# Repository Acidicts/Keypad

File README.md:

# A Numpad or Keypad
## Do as you please with it

It has:
- 16 standard 1:1 aspect ratio keys
- A 1:2 aspect ratio key
- Rotary Encoder
- Seeed Studio Xiao RP2040

The order of assembly/soldering is:
- The Diodes
- The Seeed Studio Xiao RP2040
- The Rotary Encoder
- Keys
- Keycaps Encoder Knob

This is yet to have firmware made for it as it is easier to debug with the actual hardware on hand.
Will be using either **KMK** or **QMK** most likely (kmk due to being easier to learn) and will be referencing [this](https://github.com/Acidicts/Hackpad)

The Rotary Encoder can be used as an audio knob all the way to being a selector for presets for different key setups.

Here is a render of the finished product:

Case:

<div>

</div>

https://github.com/user-attachments/assets/b589e256-21bc-4e0a-8186-24f3bf2696fe

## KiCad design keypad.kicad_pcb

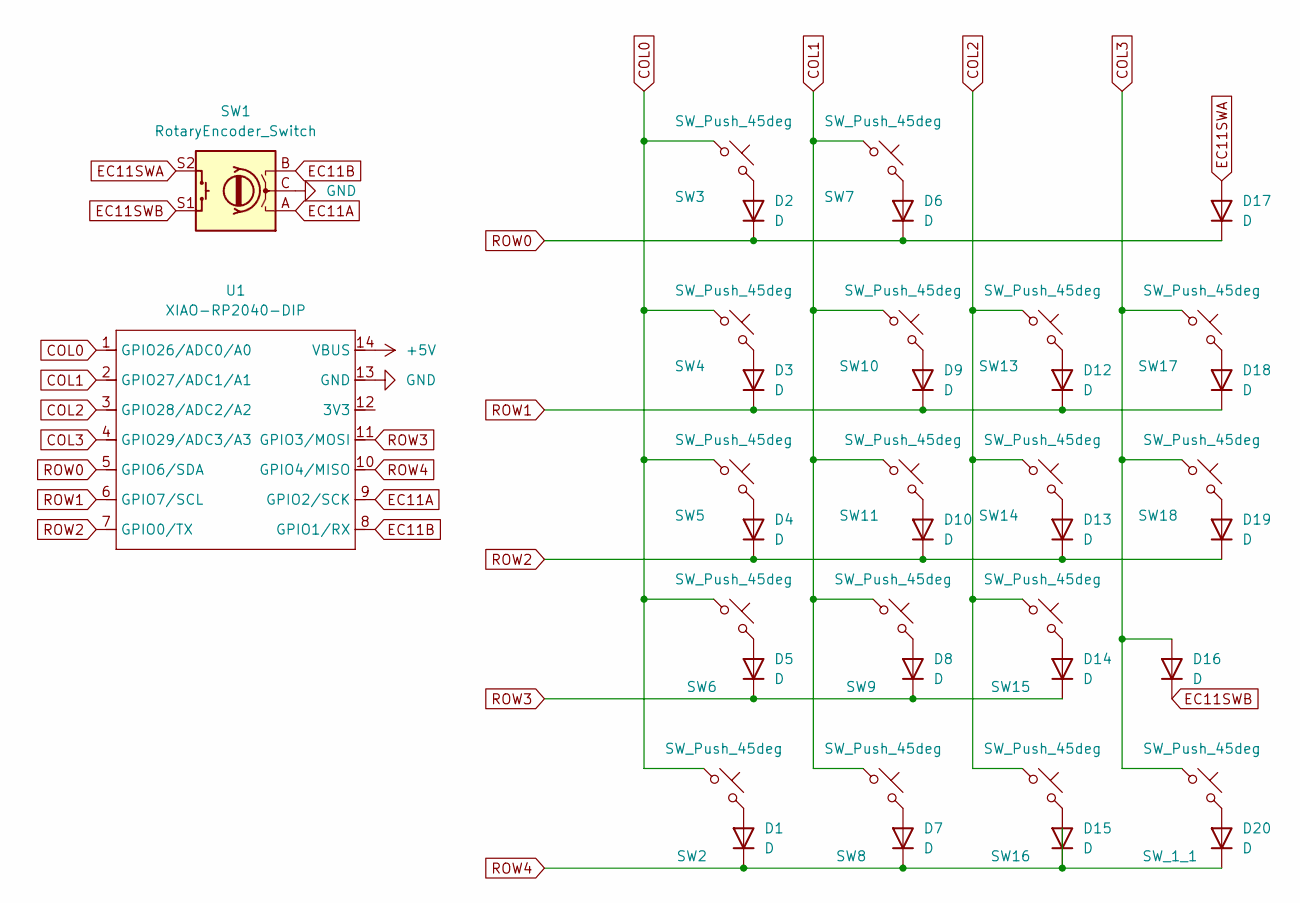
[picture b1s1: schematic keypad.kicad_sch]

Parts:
D1, D2, D3, D4, D5, D6, D7, D8, D9, D10, D12, D13, D14, D15, D16, D17, D18, D19, D20: D; D_SOD-123
SW1: RotaryEncoder_Switch; RotaryEncoder_Alps_EC11E-Switch_Vertical_H20mm
SW2, SW3, SW4, SW5, SW6, SW7, SW8, SW9, SW10, SW11, SW13, SW14, SW15, SW16, SW17, SW18: SW_Push_45deg; SW_Cherry_MX_1.00u_PCB
SW_1_1: SW_Push_45deg; SW_Cherry_MX_1.00u_PCB
U1: XIAO-RP2040-DIP

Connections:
+5V: U1.14 (VBUS)
COL0: SW2.1, SW3.1, SW4.1, SW5.1, SW6.1, U1.1 (GPIO26/ADC0/A0)
COL1: SW7.1, SW8.1, SW9.1, SW10.1, SW11.1, U1.2 (GPIO27/ADC1/A1)
COL2: SW13.1, SW14.1, SW15.1, SW16.1, U1.3 (GPIO28/ADC2/A2)
COL3: D16.2 (A), SW17.1, SW18.1, SW_1_1.1, U1.4 (GPIO29/ADC3/A3)
EC11A: SW1.A, U1.9 (GPIO2/SCK)
EC11B: SW1.B, U1.8 (GPIO1/RX)
EC11SWA: D17.2 (A), SW1.S2
EC11SWB: D16.1 (K), SW1.S1
GND: SW1.C, SW1.MP, U1.13 (GND)
unnamed: D1.2 (A), SW2.2
unnamed: D2.2 (A), SW3.2
unnamed: D3.2 (A), SW4.2
unnamed: D4.2 (A), SW5.2
unnamed: D5.2 (A), SW6.2
unnamed: D6.2 (A), SW7.2
unnamed: D7.2 (A), SW8.2
unnamed: D8.2 (A), SW9.2
unnamed: D9.2 (A), SW10.2
unnamed: D10.2 (A), SW11.2
unnamed: D12.2 (A), SW13.2
unnamed: D13.2 (A), SW14.2
unnamed: D14.2 (A), SW15.2
unnamed: D15.2 (A), SW16.2
unnamed: D18.2 (A), SW17.2
unnamed: D19.2 (A), SW18.2
unnamed: D20.2 (A), SW_1_1.2
ROW0: D2.1 (K), D6.1 (K), D17.1 (K), U1.5 (GPIO6/SDA)
ROW1: D3.1 (K), D9.1 (K), D12.1 (K), D18.1 (K), U1.6 (GPIO7/SCL)
ROW2: D4.1 (K), D10.1 (K), D13.1 (K), D19.1 (K), U1.7 (GPIO0/TX)
ROW3: D5.1 (K), D8.1 (K), D14.1 (K), U1.11 (GPIO3/MOSI)
ROW4: D1.1 (K), D7.1 (K), D15.1 (K), D20.1 (K), U1.10 (GPIO4/MISO)

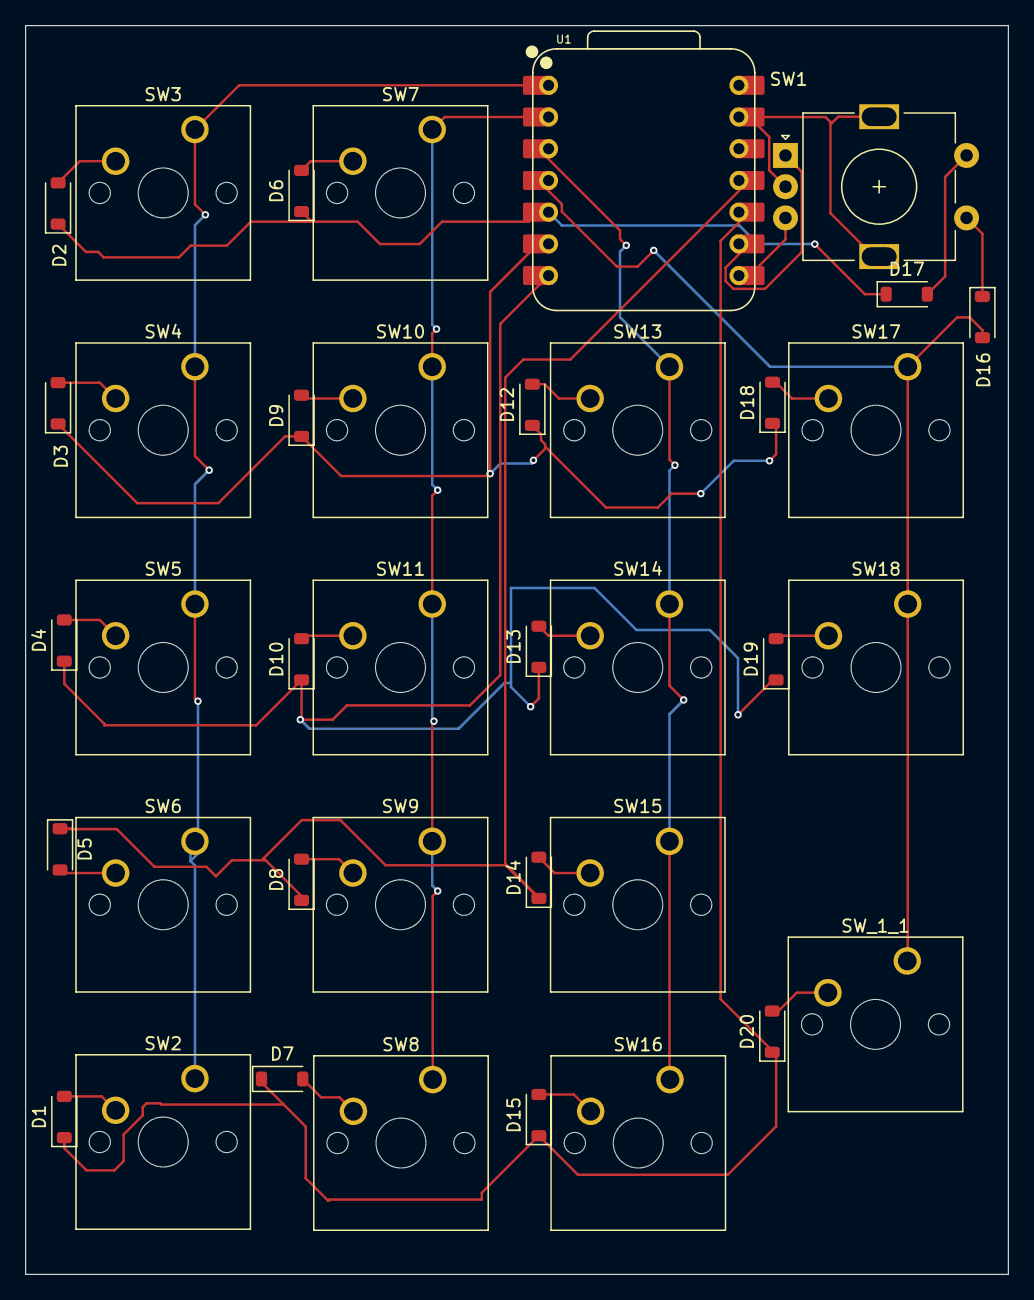
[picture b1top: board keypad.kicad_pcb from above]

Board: 2 copper layers, 78.7 x 100.0 mm, 38 parts (0 on the bottom side), 31 nets.

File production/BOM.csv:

Comment,Designator,Footprint,JLCPCB Part #?optional?
BAV16W,"D1,D2,D3,D4,D5,D6,D7,D8,D9,D10,D12,D13,D14,D15,D16,D17,D18,D19,D20",SOD123,

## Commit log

2025-10-20 Number list items in JOURNAL.md
2025-10-22 Rename keypad_case.3mf to case/keypad_case.3mf
2025-10-22 Rename gerber.zip to production/gerber.zip
2025-10-23 Fix prices and formatting in BOM.csv
    Updated the BOM.csv file to correct the price of Diodes and adjust the formatting.
2025-10-23 Fix total price in BOM.csv
    Updated total price in BOM.csv.
2025-10-23 Fix total cost in BOM.csv
    Updated total cost due to changes in item prices.
2025-11-15 Firmware Upload
2025-11-17 Rename keypad_case.3mf to bottom.3mf
2026-02-05 Change video link to an image link in README
